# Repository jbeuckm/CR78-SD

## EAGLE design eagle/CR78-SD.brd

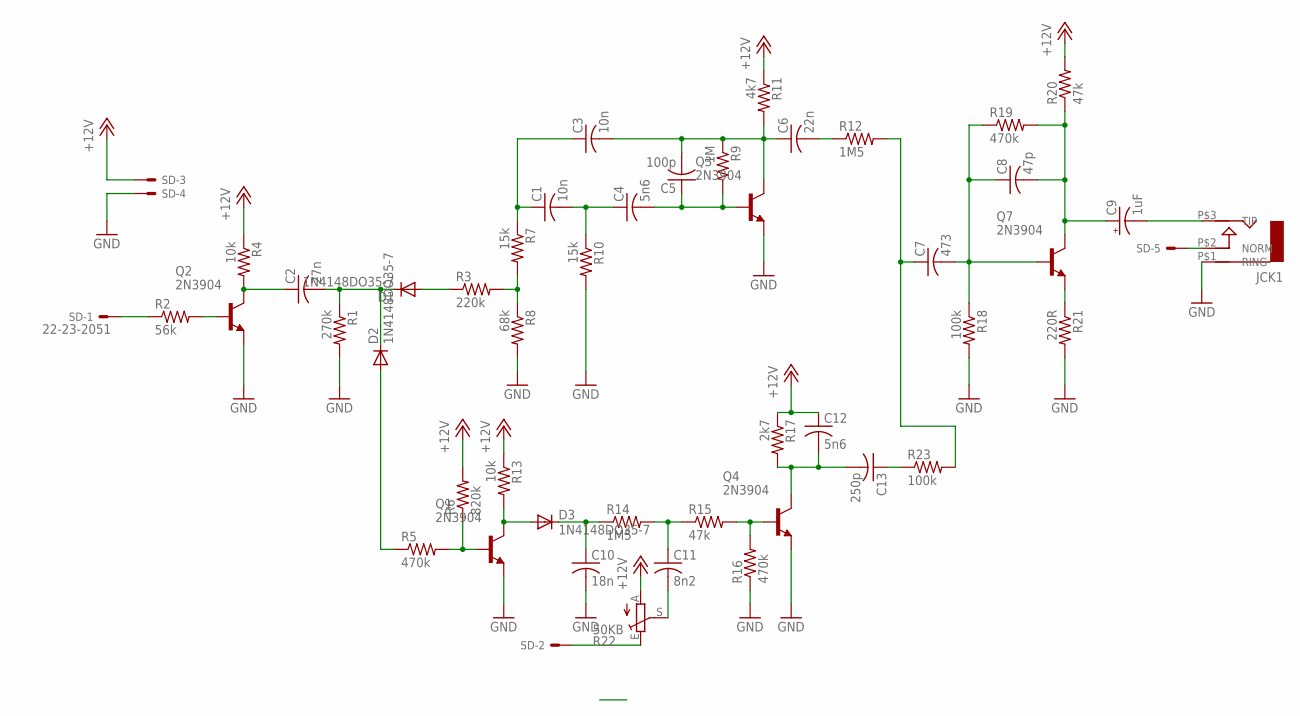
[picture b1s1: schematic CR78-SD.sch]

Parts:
C1, C3: 10n; C050-025X075
C2: 27n; C050-025X075
C4, C12: 5n6; C050-025X075
C5: 100p; C050-025X075
C6: 22n; C050-025X075
C7: 473; C050-025X075
C8: 47p; C050-025X075
C9: 1uF; B45181B
C10: 18n; C050-025X075
C11: 8n2; C050-025X075
C13: 250p; C050-025X075
D1, D2, D3: 1N4148DO35-7; DO35-7
JCK1: AUDIO-JACK; ERTHENVAR-JACK-90DEG
Q1, Q2, Q3, Q4, Q7: 2N3904; TO92
R1: 270k; 0207/7
R2: 56k; 0207/7
R3: 220k; 0207/7
R4, R13: 10k; 0207/7
R5, R16, R19: 470k; 0207/7
R6: 820k; 0207/7
R7, R10: 15k; 0207/7
R8: 68k; 0207/7
R9: 1M; 0207/7
R11: 4k7; 0207/7
R12, R14: 1M5; 0207/7
R15, R20: 47k; 0207/7
R17: 2k7; 0207/7
R18, R23: 100k; 0207/7
R21: 220R; 0207/7
R22: 50KB; B64Y
SD: 22-23-2051

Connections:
+12V: C12.1, R4.1, R6.2, R11.1, R13.1, R17.1, R20.2, R22.A, SD.3
GND: C10.2, JCK1.P$1 (RING), Q1.3 (E), Q2.3 (E), Q3.3 (E), Q4.3 (E), R1.2, R8.2, R10.2, R16.1, R18.2, R21.2, SD.4
unnamed: D1.A, R3.1
unnamed: C2.2, D1.C, D2.C, R1.1
unnamed: D2.A, R5.1
unnamed: R3.2, R7.2, R8.1
unnamed: C3.2, C5.2, C6.1, Q3.1 (C), R9.1, R11.2
unnamed: C1.2, C4.1, R10.1
unnamed: JCK1.P$2 (NORM), SD.5
unnamed: C1.1, C3.1, R7.1
unnamed: C4.2, C5.1, Q3.2 (B), R9.2
unnamed: D3.A, Q1.1 (C), R13.2
unnamed: R2.1, SD.1
unnamed: C6.2, R12.1
unnamed: C7.1, R12.2, R23.2
unnamed: Q1.2 (B), R5.2, R6.1
unnamed: Q7.3 (E), R21.1
unnamed: C8.2, C9.+, Q7.1 (C), R19.2, R20.1
unnamed: C10.1, D3.C, R14.1
unnamed: C7.2, C8.1, Q7.2 (B), R18.1, R19.1
unnamed: C9.-, JCK1.P$3 (TIP)
unnamed: C11.1, R14.2, R15.1
unnamed: Q4.2 (B), R15.2, R16.2
unnamed: C11.2, R22.S
unnamed: R22.E, SD.2
unnamed: C12.2, C13.2, Q4.1 (C), R17.2
unnamed: C13.1, R23.1
unnamed: C2.1, Q2.1 (C), R4.2
unnamed: Q2.2 (B), R2.2

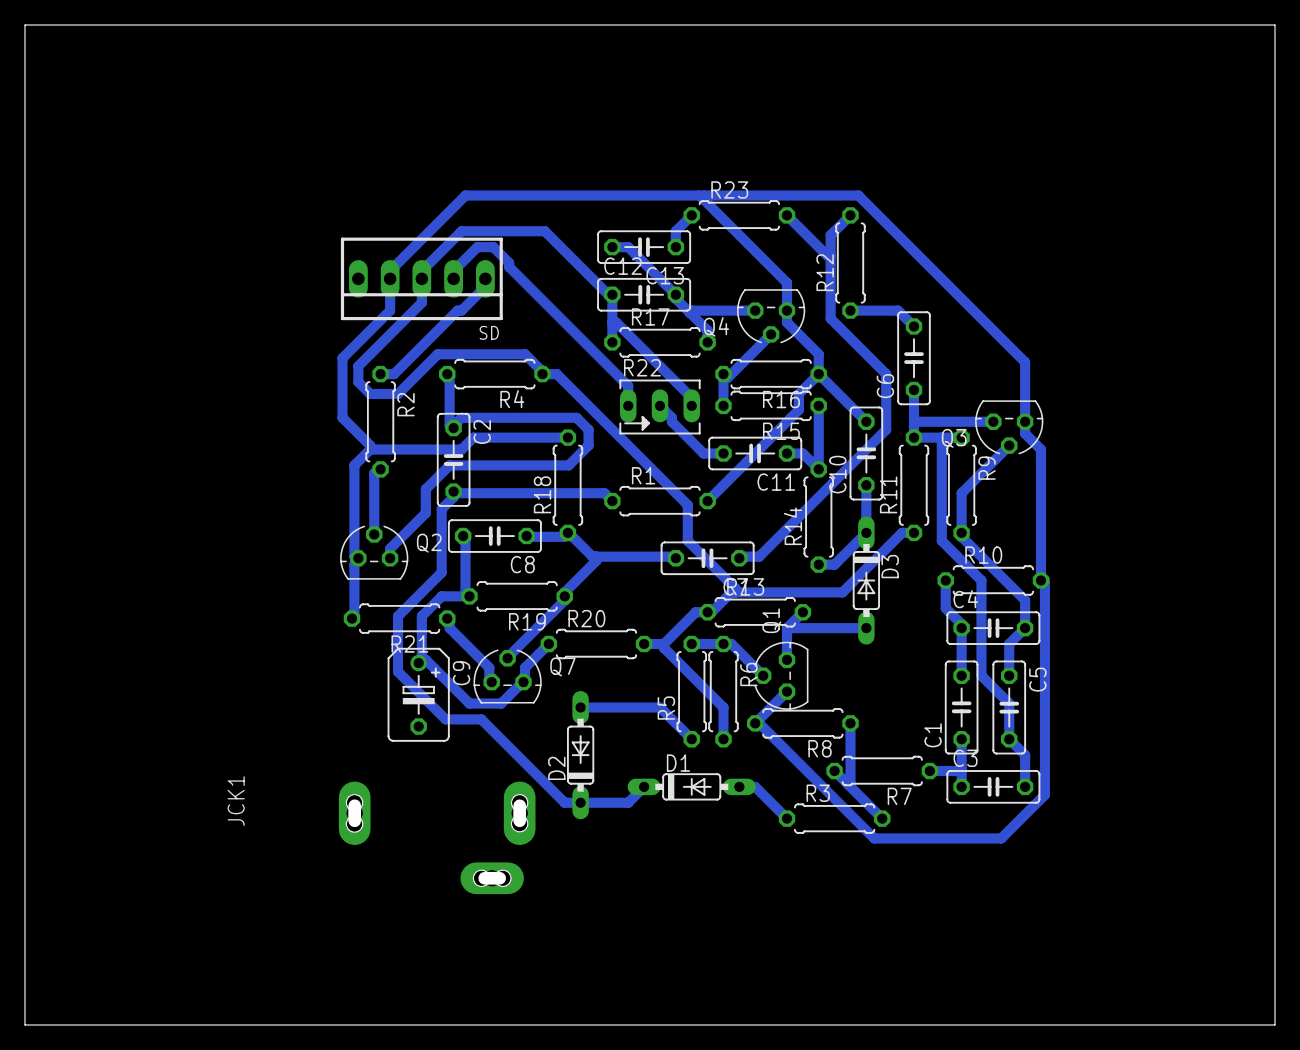
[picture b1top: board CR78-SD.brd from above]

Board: 2 copper layers, 100.0 x 80.0 mm, 46 parts (0 on the bottom side), 29 nets.

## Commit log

2016-06-09 more schemo
2016-06-09 schemo
2016-06-10 layout begun
2016-06-10 95pct auto
2016-06-10 last two routes
2016-06-10 routed and cutout
2016-06-10 tweaked smaller
2016-06-11 gcode
